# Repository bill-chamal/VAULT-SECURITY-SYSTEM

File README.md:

# Safe Security System

The Safe Security System monitors for changes in temperature and light while a safe is closed. If a minimum threshold is exceeded, the system notifies the owner only when the safe is opened normally.

<p>This repository contains Kicad and Tinkercad files</p>

<h2>About:</h2>
<p><b>Author: </b><a href="https://github.com/bill-chamal">Bill Chamalidis</a> University of Macedonia</p>

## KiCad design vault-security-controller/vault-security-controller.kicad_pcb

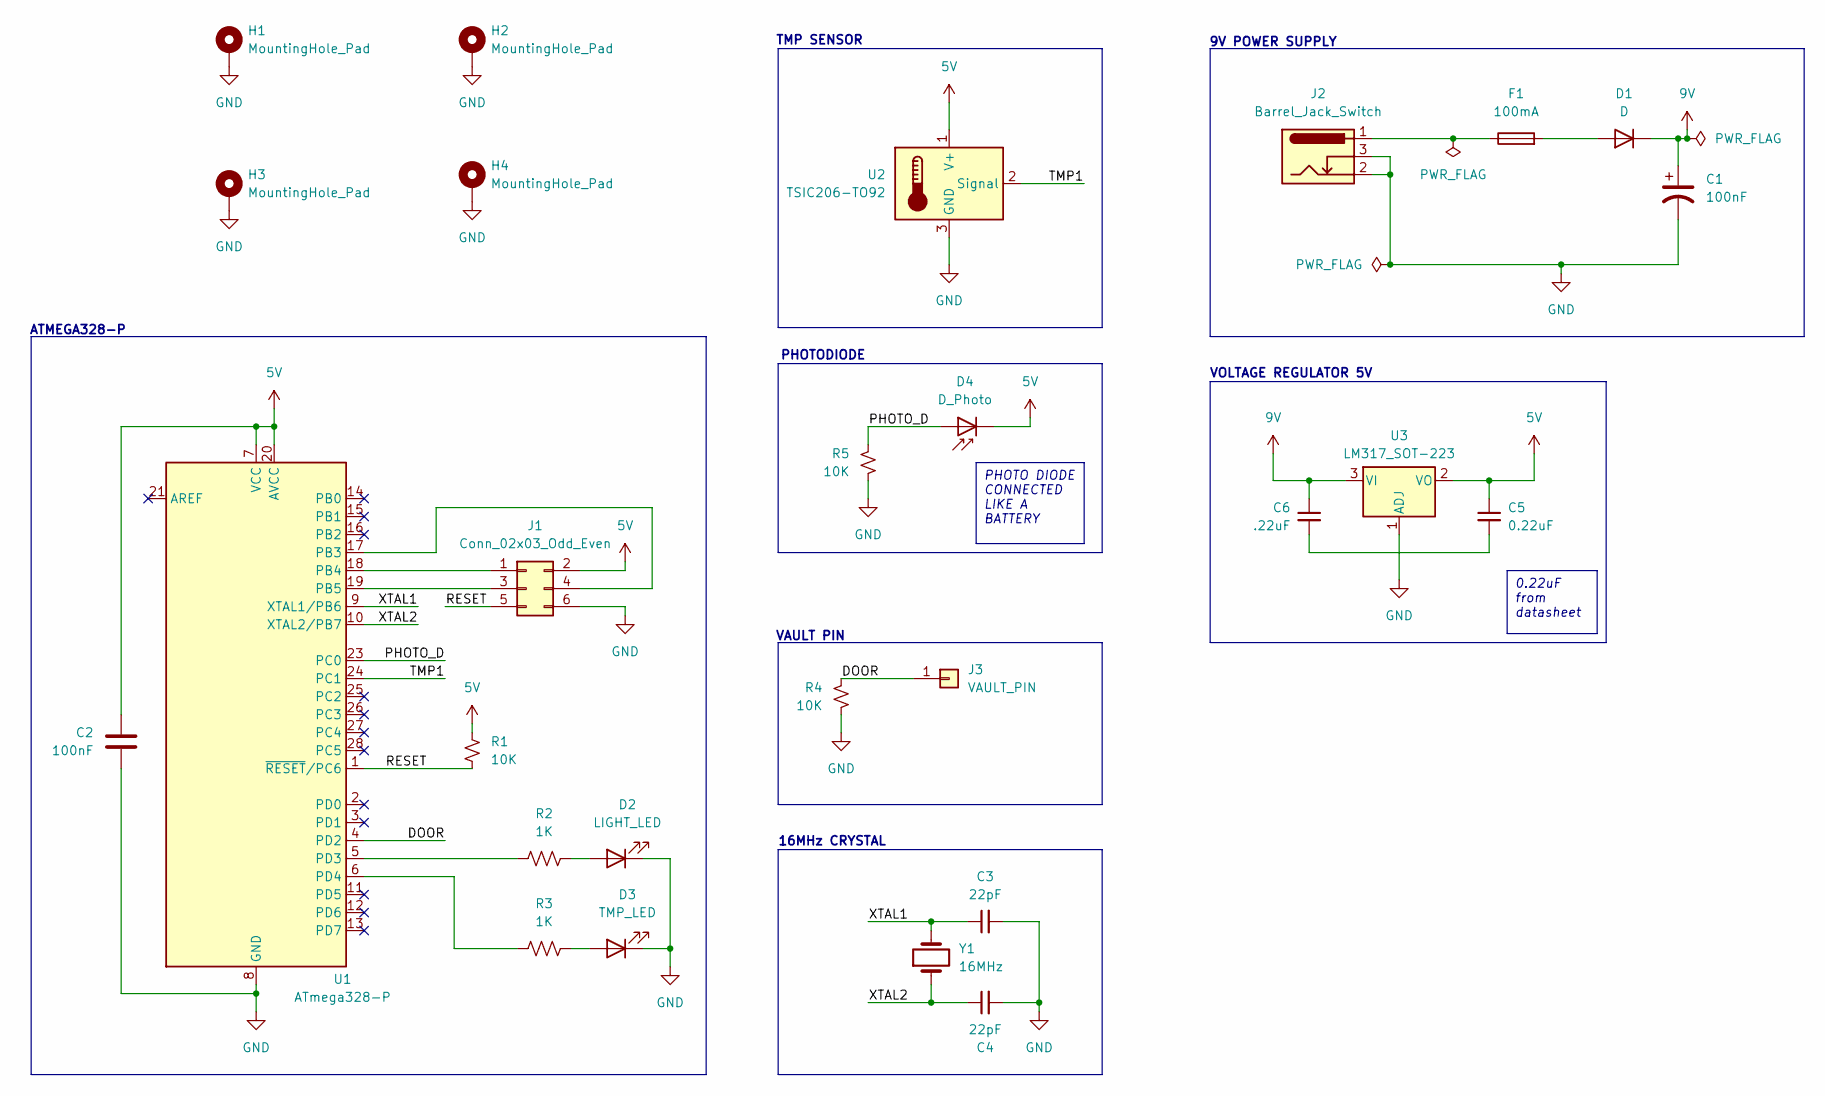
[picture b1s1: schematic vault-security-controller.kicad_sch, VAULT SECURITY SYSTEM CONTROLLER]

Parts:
C1: 100nF; CP_EIA-3216-12_Kemet-S
C2: 100nF; C_0805_2012Metric
C3, C4: 22pF; C_0402_1005Metric
C5: 0.22uF; C_0603_1608Metric
C6: .22uF; C_0603_1608Metric
D1: D; D_SMA
D2: LIGHT_LED; LED_D5.0mm
D3: TMP_LED; LED_D5.0mm
D4: D_Photo; LED_D5.0mm_IRBlack
F1: 100mA; Fuse_0805_2012Metric
H1, H2, H3, H4: MountingHole_Pad; MountingHole_2.7mm_M2.5_Pad_Via
J1: Conn_02x03_Odd_Even; PinHeader_2x03_P2.54mm_Vertical
J2: Barrel_Jack_Switch; BarrelJack_Horizontal
J3: VAULT_PIN; PinSocket_1x01_P2.54mm_Horizontal
R1, R4, R5: 10K; R_0805_2012Metric
R2, R3: 1K; R_0402_1005Metric
U1: ATmega328-P; DIP-28_W7.62mm
U2: TSIC206-TO92; TO-92_Inline
U3: LM317_SOT-223; SOT-223-3_TabPin2
Y1: 16MHz; Crystal_SMD_HC49-SD

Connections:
5V: C2.1, C5.1, D4.1 (K), J1.2, R1.2, U1.7 (VCC), U1.20 (AVCC), U2.1 (V+), U3.2 (VO)
9V: C1.1, C6.1, D1.1 (K), U3.3 (VI)
/DOOR: J3.1, R4.2, U1.4 (PD2)
/PHOTO_D: D4.2 (A), R5.2, U1.23 (PC0)
/RESET: J1.5, R1.1, U1.1 (~RESET/PC6)
/TMP1: U1.24 (PC1), U2.2 (Signal)
/XTAL1: C3.1, U1.9 (XTAL1/PB6), Y1.2
/XTAL2: C4.1, U1.10 (XTAL2/PB7), Y1.1
GND: C1.2, C2.2, C3.2, C4.2, D2.1 (K), D3.1 (K), H1.1, H2.1, H3.1, H4.1, J1.6, J2.2, J2.3, R4.1, R5.1, U1.8 (GND), U1.22 (GND), U2.3 (GND), U3.1 (ADJ)
unnamed: C5.2, C6.2
unnamed: D1.2 (A), F1.2
unnamed: D2.2 (A), R2.2
unnamed: D3.2 (A), R3.2
unnamed: F1.1, J2.1
unnamed: J1.1, U1.18 (PB4)
unnamed: J1.3, U1.19 (PB5)
unnamed: J1.4, U1.17 (PB3)
unnamed: R2.1, U1.5 (PD3)
unnamed: R3.1, U1.6 (PD4)

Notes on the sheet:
0.22uF from datasheet
PHOTO DIODE CONNECTED LIKE A BATTERY
9V POWER SUPPLY
VAULT PIN
ATMEGA328-P
VOLTAGE REGULATOR 5V
TMP SENSOR
PHOTODIODE
16MHz CRYSTAL

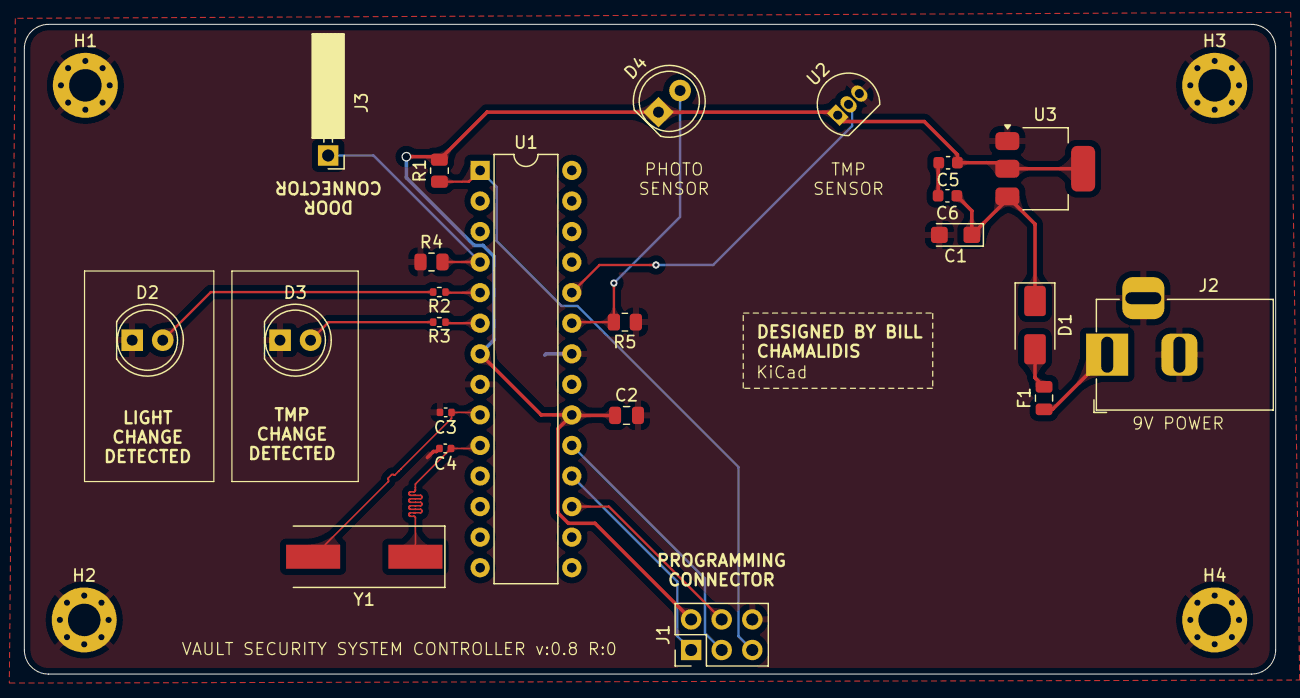
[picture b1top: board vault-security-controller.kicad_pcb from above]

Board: 2 copper layers, 104.0 x 54.0 mm, 27 parts (0 on the bottom side), 19 nets.

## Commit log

2025-02-21 main
2025-02-21 id removed
